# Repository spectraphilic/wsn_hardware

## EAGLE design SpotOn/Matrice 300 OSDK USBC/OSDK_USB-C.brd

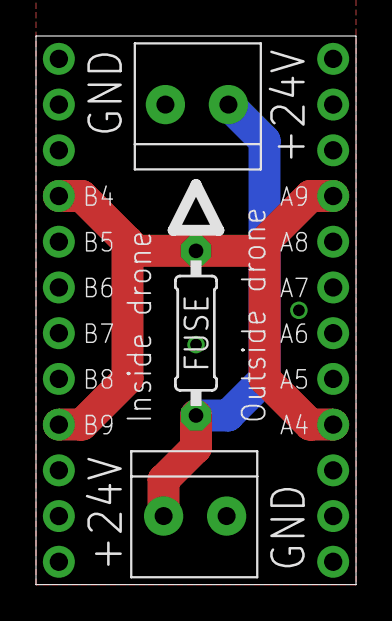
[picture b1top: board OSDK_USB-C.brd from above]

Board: 2 copper layers, 17.8 x 30.5 mm, 5 parts (0 on the bottom side), 3 nets.

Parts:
A: 1X12-CB
B: 1X12-CB
FUSE: 0207/9
J1, J2: ADAFRUIT_1X2-3.5MM

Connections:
GND: A.1, A.12, B.1, B.7, B.8, B.12, J1.2, J2.2
MAIN: A.4, A.9, B.4, B.9, FUSE.2
MIAN-F: FUSE.1, J1.1, J2.1

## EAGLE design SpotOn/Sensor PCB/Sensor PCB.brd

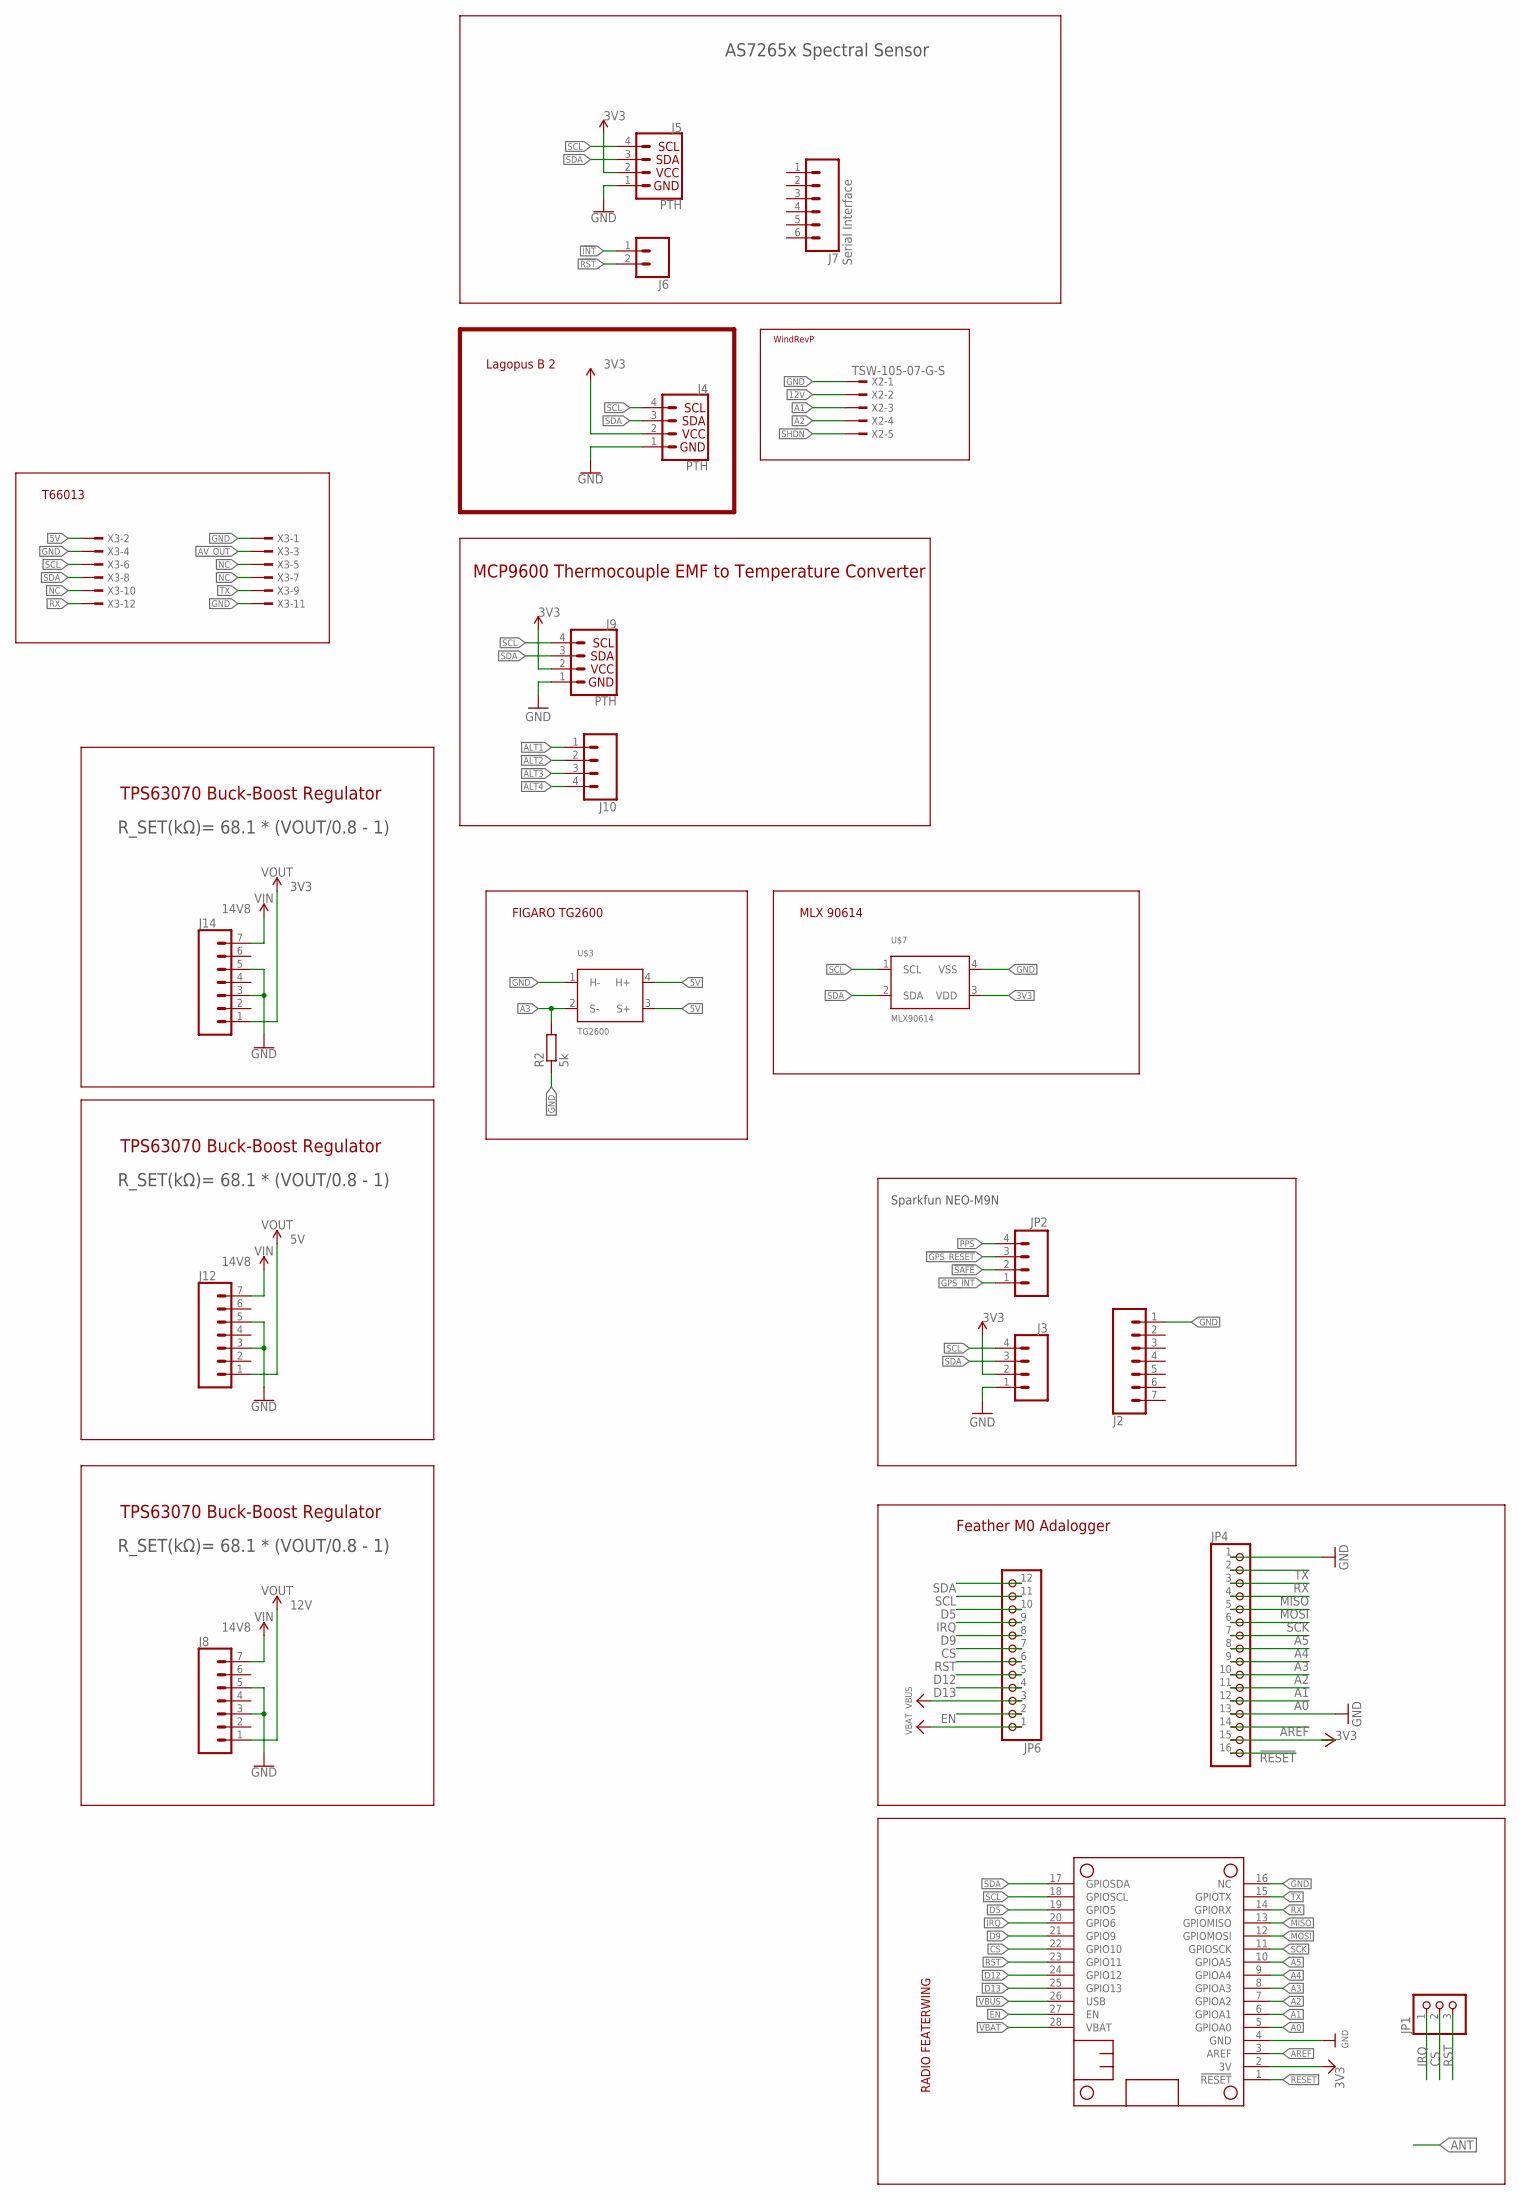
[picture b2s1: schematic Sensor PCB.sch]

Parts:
J2, J8, J12, J14: CONN_07NO_SILK; 1X07_NO_SILK
J3, J10: CONN_041X04_NO_SILK; 1X04_NO_SILK
J4, J5, J9: PTH; 1X04_NO_SILK
J6: CONN_021X02_NO_SILK; 1X02_NO_SILK
J7: Serial Interface; 1X06_NO_SILK
JP1: HEADER-1X376MIL; 1X03_ROUND_76
JP2: CONN_041X04_NO_SILK; 1X04_NO_SILK
JP4: HEADER-1X16ROUND; 1X16_ROUND
JP6: HEADER-1X12; 1X12_ROUND
MS2: FEATHERWING_NOHOLES
R2: 5k; 0207/7
U$3: TG2600; TO-5
U$7: MLX90614; TO-39
X2: TSW-105-07-G-S; TSW-105-XX-G-S
X3: TSW-106-07-G-D; TSW-106-XX-G-D

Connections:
3V3: J3.2, J4.2 (VCC), J5.2, J9.2, J14.1, JP4.15, MS2.2 (3V), U$7.3 (VDD)
5V: J12.1, U$3.3 (S+), U$3.4 (H+), X3.2
12V: J8.1, X2.2
14V8: J8.7, J12.7, J14.7
!ALT1: J10.1
!ALT2: J10.2
!ALT3: J10.3
!ALT4: J10.4
!GPS_RESET: JP2.3
!INT: J6.1
!RESET: JP4.16
!RST: J6.2
!SAFE: JP2.2
A0: JP4.12, MS2.5 (GPIOA0)
A1: JP4.11, MS2.6 (GPIOA1), X2.3
A2: JP4.10, MS2.7 (GPIOA2), X2.4
A3: JP4.9, MS2.8 (GPIOA3), R2.2, U$3.2 (S-)
A4: JP4.8, MS2.9 (GPIOA4)
A5: JP4.7, MS2.10 (GPIOA5)
AREF: JP4.14, MS2.3 (AREF)
AV_OUT: X3.3
CS: JP1.2, JP6.7, MS2.22 (GPIO10)
D5: JP6.10, MS2.19 (GPIO5)
D9: JP6.8, MS2.21 (GPIO9)
D12: JP6.5, MS2.24 (GPIO12)
D13: JP6.4, MS2.25 (GPIO13)
EN: JP6.2, MS2.27 (EN)
GND: J2.1, J3.1, J4.1 (GND), J5.1, J8.3, J8.5, J9.1, J12.3, J12.5, J14.3, J14.5, JP4.1, JP4.13, MS2.4 (GND), MS2.16 (NC), R2.1, U$3.1 (H-), U$7.4 (VSS), X2.1, X3.1, X3.4, X3.11
GPS_INT: JP2.1
IRQ: JP1.1, JP6.9, MS2.20 (GPIO6)
MISO: JP4.4, MS2.13 (GPIOMISO)
MOSI: JP4.5, MS2.12 (GPIOMOSI)
NC: X3.5, X3.7, X3.10
PPS: JP2.4
RESET: MS2.1 (!RESET)
RST: JP1.3, JP6.6, MS2.23 (GPIO11)
RX: JP4.3, MS2.14 (GPIORX), X3.12
SCK: JP4.6, MS2.11 (GPIOSCK)
SCL: J3.4, J4.4 (SCL), J5.4, J9.4, JP6.11, MS2.18 (GPIOSCL), U$7.1 (SCL), X3.6
SDA: J3.3, J4.3 (SDA), J5.3, J9.3, JP6.12, MS2.17 (GPIOSDA), U$7.2 (SDA), X3.8
SHDN: X2.5
TX: JP4.2, MS2.15 (GPIOTX), X3.9
VBAT: JP6.1, MS2.28 (VBAT)
VBUS: JP6.3, MS2.26 (USB)

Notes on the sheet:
RADIO FEATERWING
Feather M0 Adalogger
Sparkfun NEO-M9N
AS7265x Spectral Sensor
Lagopus B 2
WindRevP
MCP9600 Thermocouple EMF to Temperature Converter
T66013
TPS63070 Buck-Boost Regulator
R_SET(kΩ)= 68.1 * (VOUT/0.8 - 1)
FIGARO TG2600
MLX 90614

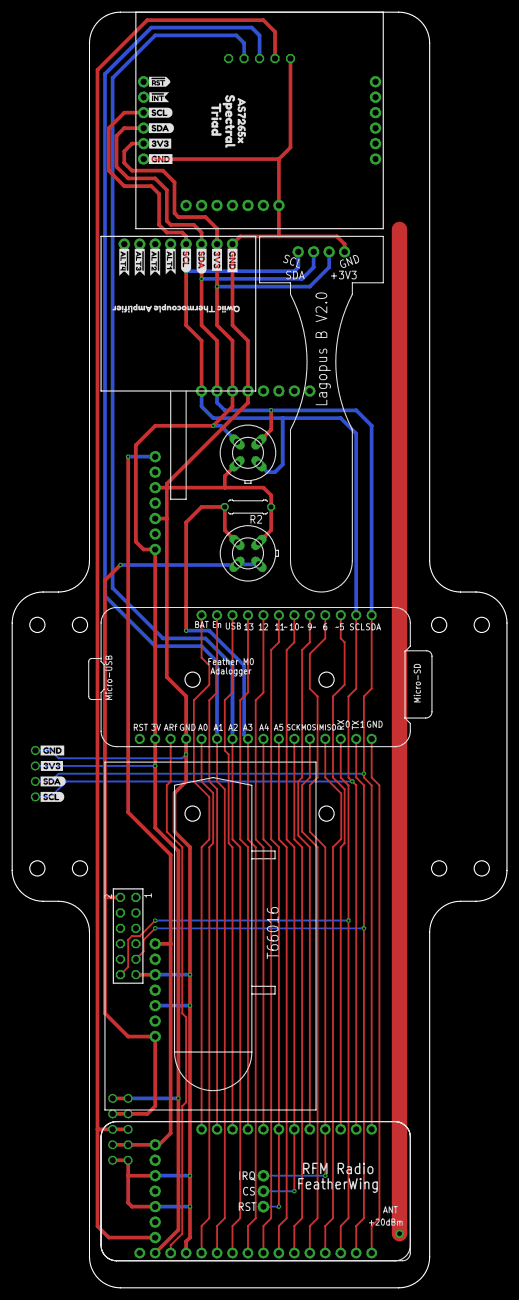
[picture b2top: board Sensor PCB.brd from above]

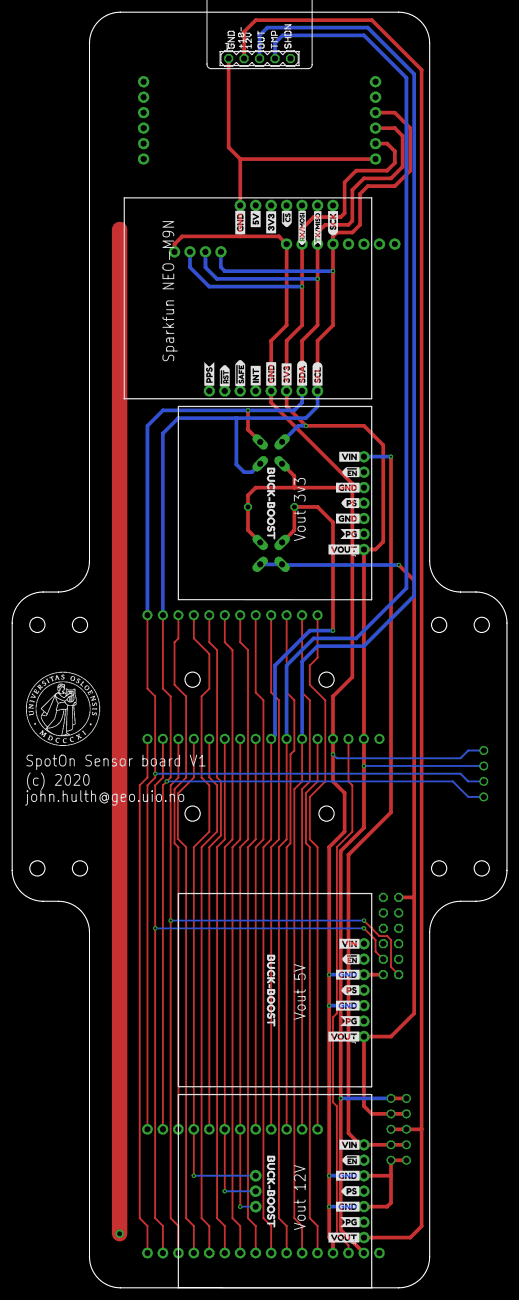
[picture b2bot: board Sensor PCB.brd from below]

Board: 2 copper layers, 81.3 x 209.6 mm, 84 parts (47 on the bottom side), 30 nets.

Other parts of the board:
U$1: UIO-LOGO-BL
U$8, U$12, U$20, U$44: GND-04
U$9, U$19, U$46: SDA-[)
U$10, U$26, U$47: SCL-[)
U$11, U$15, U$18, U$45: 3V3-04
U$13: INT8
U$14: #RST3
U$16: #SAFE1
U$17: PPS5
U$21: 5V
U$22: CS#-<]
U$23: AS7265X0
U$24: SCK-(]-04
U$25: RX#MOSI2
U$27: TX#MISO0
U$29, U$63, U$79: VIN0
U$30, U$43, U$64, U$65, U$80, U$81: GND1
U$31: GND0
U$32: 3V31
U$33: SDA2
U$34: SCL3
U$35: #ALT14
U$36: SPECTRAL1
U$37: TRIAD2
U$38: #ALT25
U$39: #ALT36
U$40: #ALT47
U$41: QWIIC_THERMOCOUPLE2
U$42: AMPLIFIER1
U$48: INT#-[<-04
U$49: RST#-[>-04
U$50, U$66, U$82: VOUT2
U$51, U$67, U$83: #EN0
U$52, U$68, U$84: PS1
U$53, U$69, U$85: PG2
U$54, U$70, U$86: BUCK#BOOST18

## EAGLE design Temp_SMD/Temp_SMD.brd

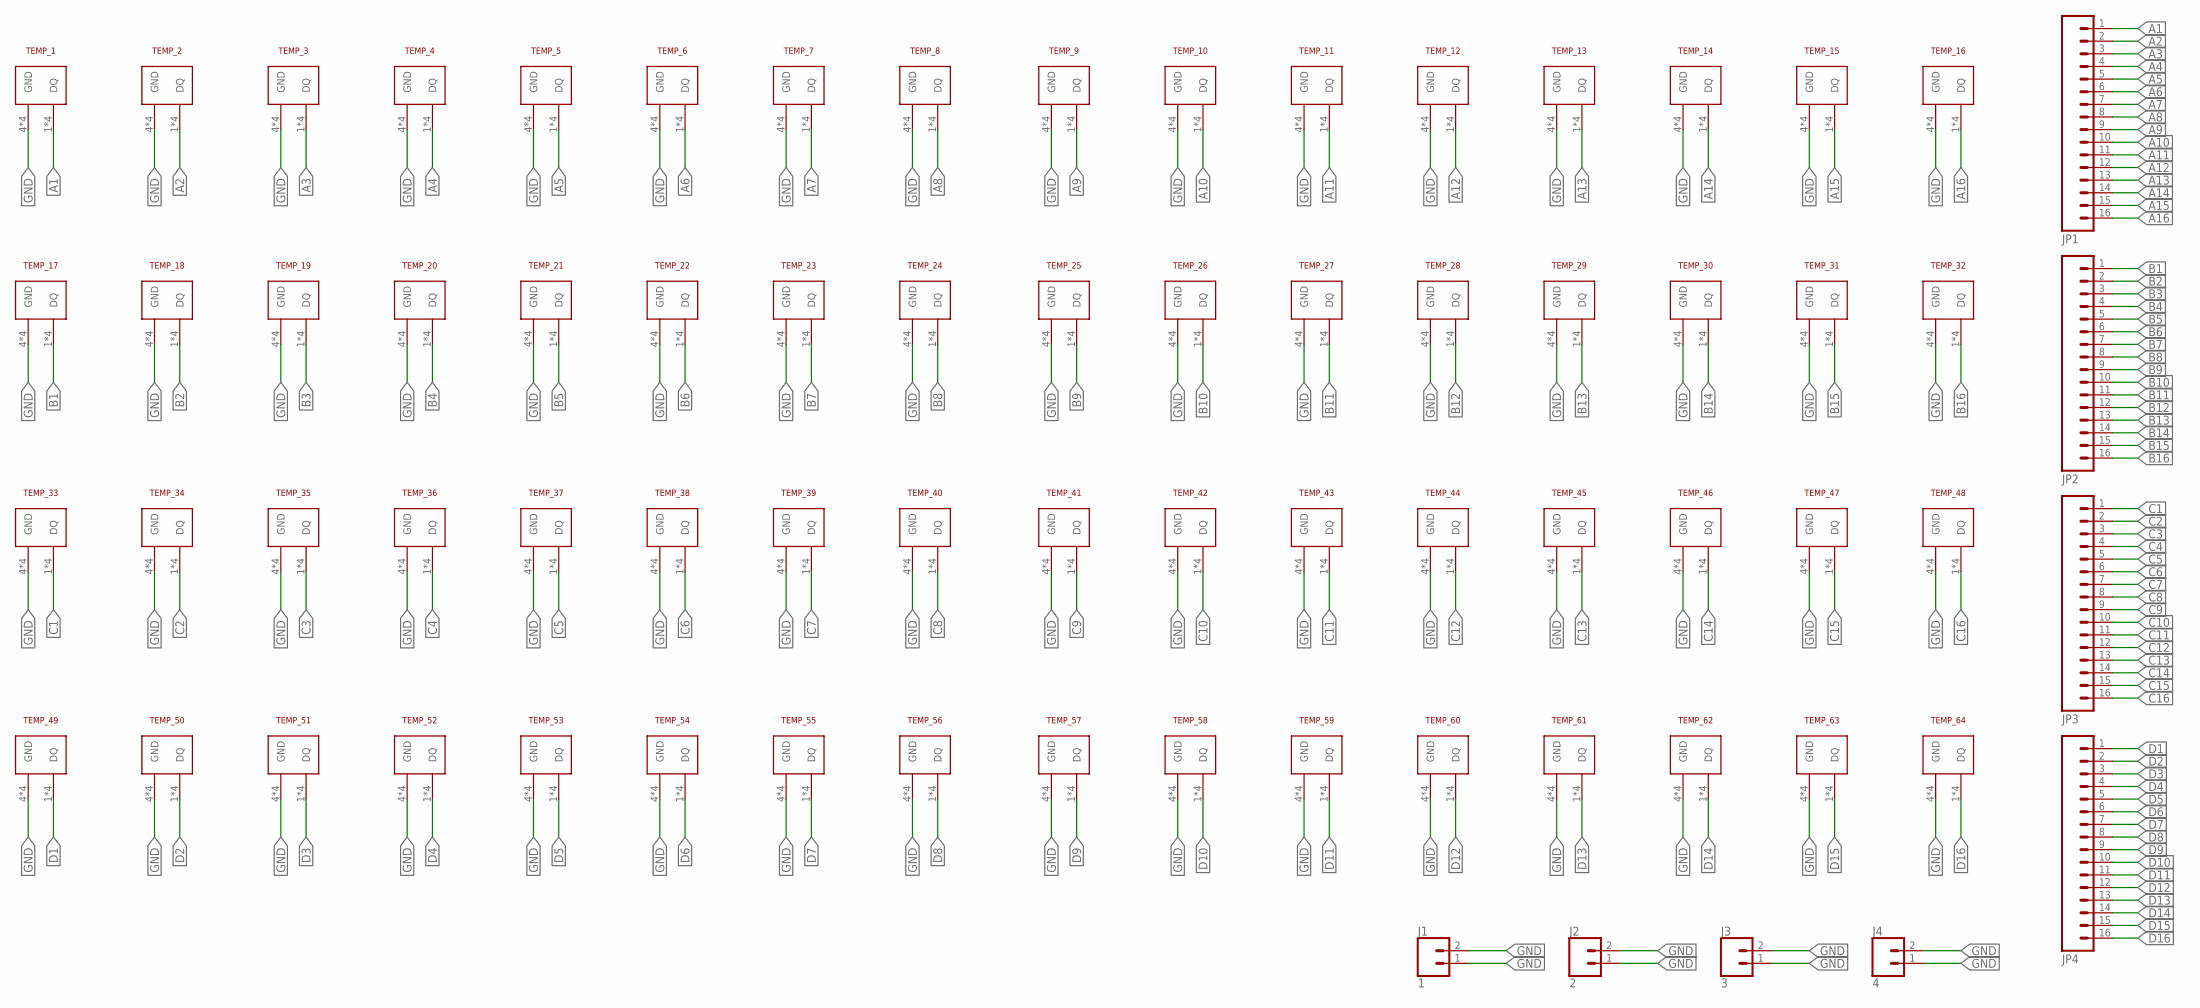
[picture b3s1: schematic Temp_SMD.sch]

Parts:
J1: 1; 1X02
J2: 2; 1X02
J3: 3; 1X02
J4: 4; 1X02
JP1, JP2, JP3, JP4: M16PTH; 1X16
TEMP_1, TEMP_2, TEMP_3, TEMP_4, TEMP_5, TEMP_6, TEMP_7, TEMP_8, TEMP_9, TEMP_10, TEMP_11, TEMP_12, TEMP_13, TEMP_14, TEMP_15, TEMP_16, TEMP_17, TEMP_18, TEMP_19, TEMP_20, TEMP_21, TEMP_22, TEMP_23, TEMP_24, TEMP_25, TEMP_26, TEMP_27, TEMP_28, TEMP_29, TEMP_30, TEMP_31, TEMP_32, TEMP_33, TEMP_34, TEMP_35, TEMP_36, TEMP_37, TEMP_38, TEMP_39, TEMP_40, TEMP_41, TEMP_42, TEMP_43, TEMP_44, TEMP_45, TEMP_46, TEMP_47, TEMP_48, TEMP_49, TEMP_50, TEMP_51, TEMP_52, TEMP_53, TEMP_54, TEMP_55, TEMP_56, TEMP_57, TEMP_58, TEMP_59, TEMP_60, TEMP_61, TEMP_62, TEMP_63, TEMP_64: SMD_TEMP

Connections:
A1: JP1.1, TEMP_1.1 (DQ), TEMP_1.DQ, TEMP_1.DQ1 (DQ), TEMP_1.DQ2 (DQ)
A2: JP1.2, TEMP_2.1 (DQ), TEMP_2.DQ, TEMP_2.DQ1 (DQ), TEMP_2.DQ2 (DQ)
A3: JP1.3, TEMP_3.1 (DQ), TEMP_3.DQ, TEMP_3.DQ1 (DQ), TEMP_3.DQ2 (DQ)
A4: JP1.4, TEMP_4.1 (DQ), TEMP_4.DQ, TEMP_4.DQ1 (DQ), TEMP_4.DQ2 (DQ)
A5: JP1.5, TEMP_5.1 (DQ), TEMP_5.DQ, TEMP_5.DQ1 (DQ), TEMP_5.DQ2 (DQ)
A6: JP1.6, TEMP_6.1 (DQ), TEMP_6.DQ, TEMP_6.DQ1 (DQ), TEMP_6.DQ2 (DQ)
A7: JP1.7, TEMP_7.1 (DQ), TEMP_7.DQ, TEMP_7.DQ1 (DQ), TEMP_7.DQ2 (DQ)
A8: JP1.8, TEMP_8.1 (DQ), TEMP_8.DQ, TEMP_8.DQ1 (DQ), TEMP_8.DQ2 (DQ)
A9: JP1.9, TEMP_9.1 (DQ), TEMP_9.DQ, TEMP_9.DQ1 (DQ), TEMP_9.DQ2 (DQ)
A10: JP1.10, TEMP_10.1 (DQ), TEMP_10.DQ, TEMP_10.DQ1 (DQ), TEMP_10.DQ2 (DQ)
A11: JP1.11, TEMP_11.1 (DQ), TEMP_11.DQ, TEMP_11.DQ1 (DQ), TEMP_11.DQ2 (DQ)
A12: JP1.12, TEMP_12.1 (DQ), TEMP_12.DQ, TEMP_12.DQ1 (DQ), TEMP_12.DQ2 (DQ)
A13: JP1.13, TEMP_13.1 (DQ), TEMP_13.DQ, TEMP_13.DQ1 (DQ), TEMP_13.DQ2 (DQ)
A14: JP1.14, TEMP_14.1 (DQ), TEMP_14.DQ, TEMP_14.DQ1 (DQ), TEMP_14.DQ2 (DQ)
A15: JP1.15, TEMP_15.1 (DQ), TEMP_15.DQ, TEMP_15.DQ1 (DQ), TEMP_15.DQ2 (DQ)
A16: JP1.16, TEMP_16.1 (DQ), TEMP_16.DQ, TEMP_16.DQ1 (DQ), TEMP_16.DQ2 (DQ)
B1: JP2.1, TEMP_17.1 (DQ), TEMP_17.DQ, TEMP_17.DQ1 (DQ), TEMP_17.DQ2 (DQ)
B2: JP2.2, TEMP_18.1 (DQ), TEMP_18.DQ, TEMP_18.DQ1 (DQ), TEMP_18.DQ2 (DQ)
B3: JP2.3, TEMP_19.1 (DQ), TEMP_19.DQ, TEMP_19.DQ1 (DQ), TEMP_19.DQ2 (DQ)
B4: JP2.4, TEMP_20.1 (DQ), TEMP_20.DQ, TEMP_20.DQ1 (DQ), TEMP_20.DQ2 (DQ)
B5: JP2.5, TEMP_21.1 (DQ), TEMP_21.DQ, TEMP_21.DQ1 (DQ), TEMP_21.DQ2 (DQ)
B6: JP2.6, TEMP_22.1 (DQ), TEMP_22.DQ, TEMP_22.DQ1 (DQ), TEMP_22.DQ2 (DQ)
B7: JP2.7, TEMP_23.1 (DQ), TEMP_23.DQ, TEMP_23.DQ1 (DQ), TEMP_23.DQ2 (DQ)
B8: JP2.8, TEMP_24.1 (DQ), TEMP_24.DQ, TEMP_24.DQ1 (DQ), TEMP_24.DQ2 (DQ)
B9: JP2.9, TEMP_25.1 (DQ), TEMP_25.DQ, TEMP_25.DQ1 (DQ), TEMP_25.DQ2 (DQ)
B10: JP2.10, TEMP_26.1 (DQ), TEMP_26.DQ, TEMP_26.DQ1 (DQ), TEMP_26.DQ2 (DQ)
B11: JP2.11, TEMP_27.1 (DQ), TEMP_27.DQ, TEMP_27.DQ1 (DQ), TEMP_27.DQ2 (DQ)
B12: JP2.12, TEMP_28.1 (DQ), TEMP_28.DQ, TEMP_28.DQ1 (DQ), TEMP_28.DQ2 (DQ)
B13: JP2.13, TEMP_29.1 (DQ), TEMP_29.DQ, TEMP_29.DQ1 (DQ), TEMP_29.DQ2 (DQ)
B14: JP2.14, TEMP_30.1 (DQ), TEMP_30.DQ, TEMP_30.DQ1 (DQ), TEMP_30.DQ2 (DQ)
B15: JP2.15, TEMP_31.1 (DQ), TEMP_31.DQ, TEMP_31.DQ1 (DQ), TEMP_31.DQ2 (DQ)
B16: JP2.16, TEMP_32.1 (DQ), TEMP_32.DQ, TEMP_32.DQ1 (DQ), TEMP_32.DQ2 (DQ)
C1: JP3.1, TEMP_33.1 (DQ), TEMP_33.DQ, TEMP_33.DQ1 (DQ), TEMP_33.DQ2 (DQ)
C2: JP3.2, TEMP_34.1 (DQ), TEMP_34.DQ, TEMP_34.DQ1 (DQ), TEMP_34.DQ2 (DQ)
C3: JP3.3, TEMP_35.1 (DQ), TEMP_35.DQ, TEMP_35.DQ1 (DQ), TEMP_35.DQ2 (DQ)
C4: JP3.4, TEMP_36.1 (DQ), TEMP_36.DQ, TEMP_36.DQ1 (DQ), TEMP_36.DQ2 (DQ)
C5: JP3.5, TEMP_37.1 (DQ), TEMP_37.DQ, TEMP_37.DQ1 (DQ), TEMP_37.DQ2 (DQ)
C6: JP3.6, TEMP_38.1 (DQ), TEMP_38.DQ, TEMP_38.DQ1 (DQ), TEMP_38.DQ2 (DQ)
C7: JP3.7, TEMP_39.1 (DQ), TEMP_39.DQ, TEMP_39.DQ1 (DQ), TEMP_39.DQ2 (DQ)
C8: JP3.8, TEMP_40.1 (DQ), TEMP_40.DQ, TEMP_40.DQ1 (DQ), TEMP_40.DQ2 (DQ)
C9: JP3.9, TEMP_41.1 (DQ), TEMP_41.DQ, TEMP_41.DQ1 (DQ), TEMP_41.DQ2 (DQ)
C10: JP3.10, TEMP_42.1 (DQ), TEMP_42.DQ, TEMP_42.DQ1 (DQ), TEMP_42.DQ2 (DQ)
C11: JP3.11, TEMP_43.1 (DQ), TEMP_43.DQ, TEMP_43.DQ1 (DQ), TEMP_43.DQ2 (DQ)
C12: JP3.12, TEMP_44.1 (DQ), TEMP_44.DQ, TEMP_44.DQ1 (DQ), TEMP_44.DQ2 (DQ)
C13: JP3.13, TEMP_45.1 (DQ), TEMP_45.DQ, TEMP_45.DQ1 (DQ), TEMP_45.DQ2 (DQ)
C14: JP3.14, TEMP_46.1 (DQ), TEMP_46.DQ, TEMP_46.DQ1 (DQ), TEMP_46.DQ2 (DQ)
C15: JP3.15, TEMP_47.1 (DQ), TEMP_47.DQ, TEMP_47.DQ1 (DQ), TEMP_47.DQ2 (DQ)
C16: JP3.16, TEMP_48.1 (DQ), TEMP_48.DQ, TEMP_48.DQ1 (DQ), TEMP_48.DQ2 (DQ)
D1: JP4.1, TEMP_49.1 (DQ), TEMP_49.DQ, TEMP_49.DQ1 (DQ), TEMP_49.DQ2 (DQ)
D2: JP4.2, TEMP_50.1 (DQ), TEMP_50.DQ, TEMP_50.DQ1 (DQ), TEMP_50.DQ2 (DQ)
D3: JP4.3, TEMP_51.1 (DQ), TEMP_51.DQ, TEMP_51.DQ1 (DQ), TEMP_51.DQ2 (DQ)
D4: JP4.4, TEMP_52.1 (DQ), TEMP_52.DQ, TEMP_52.DQ1 (DQ), TEMP_52.DQ2 (DQ)
D5: JP4.5, TEMP_53.1 (DQ), TEMP_53.DQ, TEMP_53.DQ1 (DQ), TEMP_53.DQ2 (DQ)
D6: JP4.6, TEMP_54.1 (DQ), TEMP_54.DQ, TEMP_54.DQ1 (DQ), TEMP_54.DQ2 (DQ)
D7: JP4.7, TEMP_55.1 (DQ), TEMP_55.DQ, TEMP_55.DQ1 (DQ), TEMP_55.DQ2 (DQ)
D8: JP4.8, TEMP_56.1 (DQ), TEMP_56.DQ, TEMP_56.DQ1 (DQ), TEMP_56.DQ2 (DQ)
D9: JP4.9, TEMP_57.1 (DQ), TEMP_57.DQ, TEMP_57.DQ1 (DQ), TEMP_57.DQ2 (DQ)
D10: JP4.10, TEMP_58.1 (DQ), TEMP_58.DQ, TEMP_58.DQ1 (DQ), TEMP_58.DQ2 (DQ)
D11: JP4.11, TEMP_59.1 (DQ), TEMP_59.DQ, TEMP_59.DQ1 (DQ), TEMP_59.DQ2 (DQ)
D12: JP4.12, TEMP_60.1 (DQ), TEMP_60.DQ, TEMP_60.DQ1 (DQ), TEMP_60.DQ2 (DQ)
D13: JP4.13, TEMP_61.1 (DQ), TEMP_61.DQ, TEMP_61.DQ1 (DQ), TEMP_61.DQ2 (DQ)
D14: JP4.14, TEMP_62.1 (DQ), TEMP_62.DQ, TEMP_62.DQ1 (DQ), TEMP_62.DQ2 (DQ)
D15: JP4.15, TEMP_63.1 (DQ), TEMP_63.DQ, TEMP_63.DQ1 (DQ), TEMP_63.DQ2 (DQ)
D16: JP4.16, TEMP_64.1 (DQ), TEMP_64.DQ, TEMP_64.DQ1 (DQ), TEMP_64.DQ2 (DQ)
GND: J1.1, J1.2, J2.1, J2.2, J3.1, J3.2, J4.1, J4.2, TEMP_1.4 (GND), TEMP_1.8 (GND), TEMP_1.GND1 (GND), TEMP_1.GND2 (GND), TEMP_2.4 (GND), TEMP_2.8 (GND), TEMP_2.GND1 (GND), TEMP_2.GND2 (GND), TEMP_3.4 (GND), TEMP_3.8 (GND), TEMP_3.GND1 (GND), TEMP_3.GND2 (GND), TEMP_4.4 (GND), TEMP_4.8 (GND), TEMP_4.GND1 (GND), TEMP_4.GND2 (GND), TEMP_5.4 (GND), TEMP_5.8 (GND), TEMP_5.GND1 (GND), TEMP_5.GND2 (GND), TEMP_6.4 (GND), TEMP_6.8 (GND), TEMP_6.GND1 (GND), TEMP_6.GND2 (GND), TEMP_7.4 (GND), TEMP_7.8 (GND), TEMP_7.GND1 (GND), TEMP_7.GND2 (GND), TEMP_8.4 (GND), TEMP_8.8 (GND), TEMP_8.GND1 (GND), TEMP_8.GND2 (GND), TEMP_9.4 (GND), TEMP_9.8 (GND), TEMP_9.GND1 (GND), TEMP_9.GND2 (GND), TEMP_10.4 (GND), TEMP_10.8 (GND), TEMP_10.GND1 (GND), TEMP_10.GND2 (GND), TEMP_11.4 (GND), TEMP_11.8 (GND), TEMP_11.GND1 (GND), TEMP_11.GND2 (GND), TEMP_12.4 (GND), TEMP_12.8 (GND), TEMP_12.GND1 (GND), TEMP_12.GND2 (GND), TEMP_13.4 (GND), TEMP_13.8 (GND), TEMP_13.GND1 (GND), TEMP_13.GND2 (GND), TEMP_14.4 (GND), TEMP_14.8 (GND), TEMP_14.GND1 (GND), TEMP_14.GND2 (GND), TEMP_15.4 (GND), TEMP_15.8 (GND), TEMP_15.GND1 (GND), TEMP_15.GND2 (GND), TEMP_16.4 (GND), TEMP_16.8 (GND), TEMP_16.GND1 (GND), TEMP_16.GND2 (GND), TEMP_17.4 (GND), TEMP_17.8 (GND), TEMP_17.GND1 (GND), TEMP_17.GND2 (GND), TEMP_18.4 (GND), TEMP_18.8 (GND), TEMP_18.GND1 (GND), TEMP_18.GND2 (GND), TEMP_19.4 (GND), TEMP_19.8 (GND), TEMP_19.GND1 (GND), TEMP_19.GND2 (GND), TEMP_20.4 (GND), TEMP_20.8 (GND), TEMP_20.GND1 (GND), TEMP_20.GND2 (GND), TEMP_21.4 (GND), TEMP_21.8 (GND), TEMP_21.GND1 (GND), TEMP_21.GND2 (GND), TEMP_22.4 (GND), TEMP_22.8 (GND), TEMP_22.GND1 (GND), TEMP_22.GND2 (GND), TEMP_23.4 (GND), TEMP_23.8 (GND), TEMP_23.GND1 (GND), TEMP_23.GND2 (GND), TEMP_24.4 (GND), TEMP_24.8 (GND), TEMP_24.GND1 (GND), TEMP_24.GND2 (GND), TEMP_25.4 (GND), TEMP_25.8 (GND), TEMP_25.GND1 (GND), TEMP_25.GND2 (GND), TEMP_26.4 (GND), TEMP_26.8 (GND), TEMP_26.GND1 (GND), TEMP_26.GND2 (GND), TEMP_27.4 (GND)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

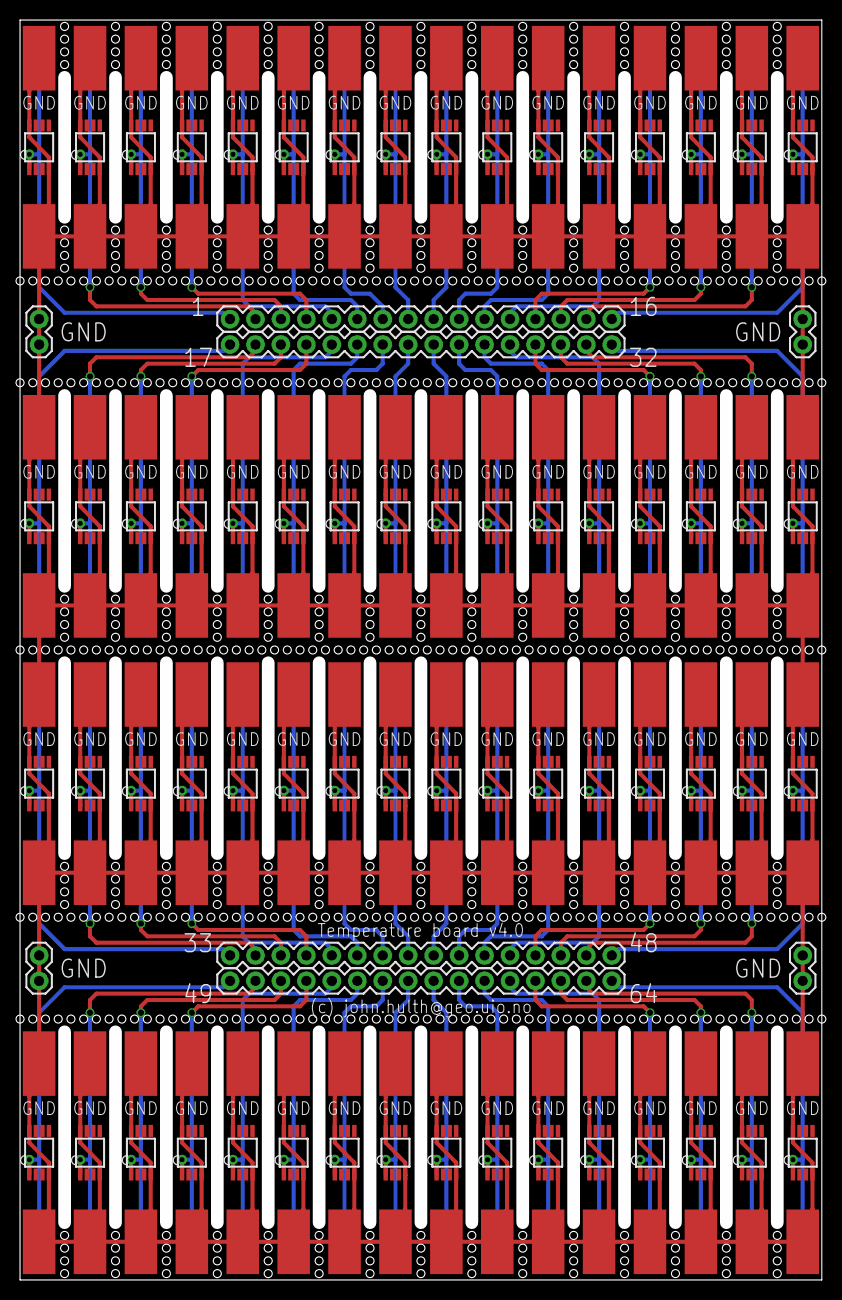
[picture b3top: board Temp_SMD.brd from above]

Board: 2 copper layers, 80.0 x 125.7 mm, 72 parts (0 on the bottom side), 65 nets.

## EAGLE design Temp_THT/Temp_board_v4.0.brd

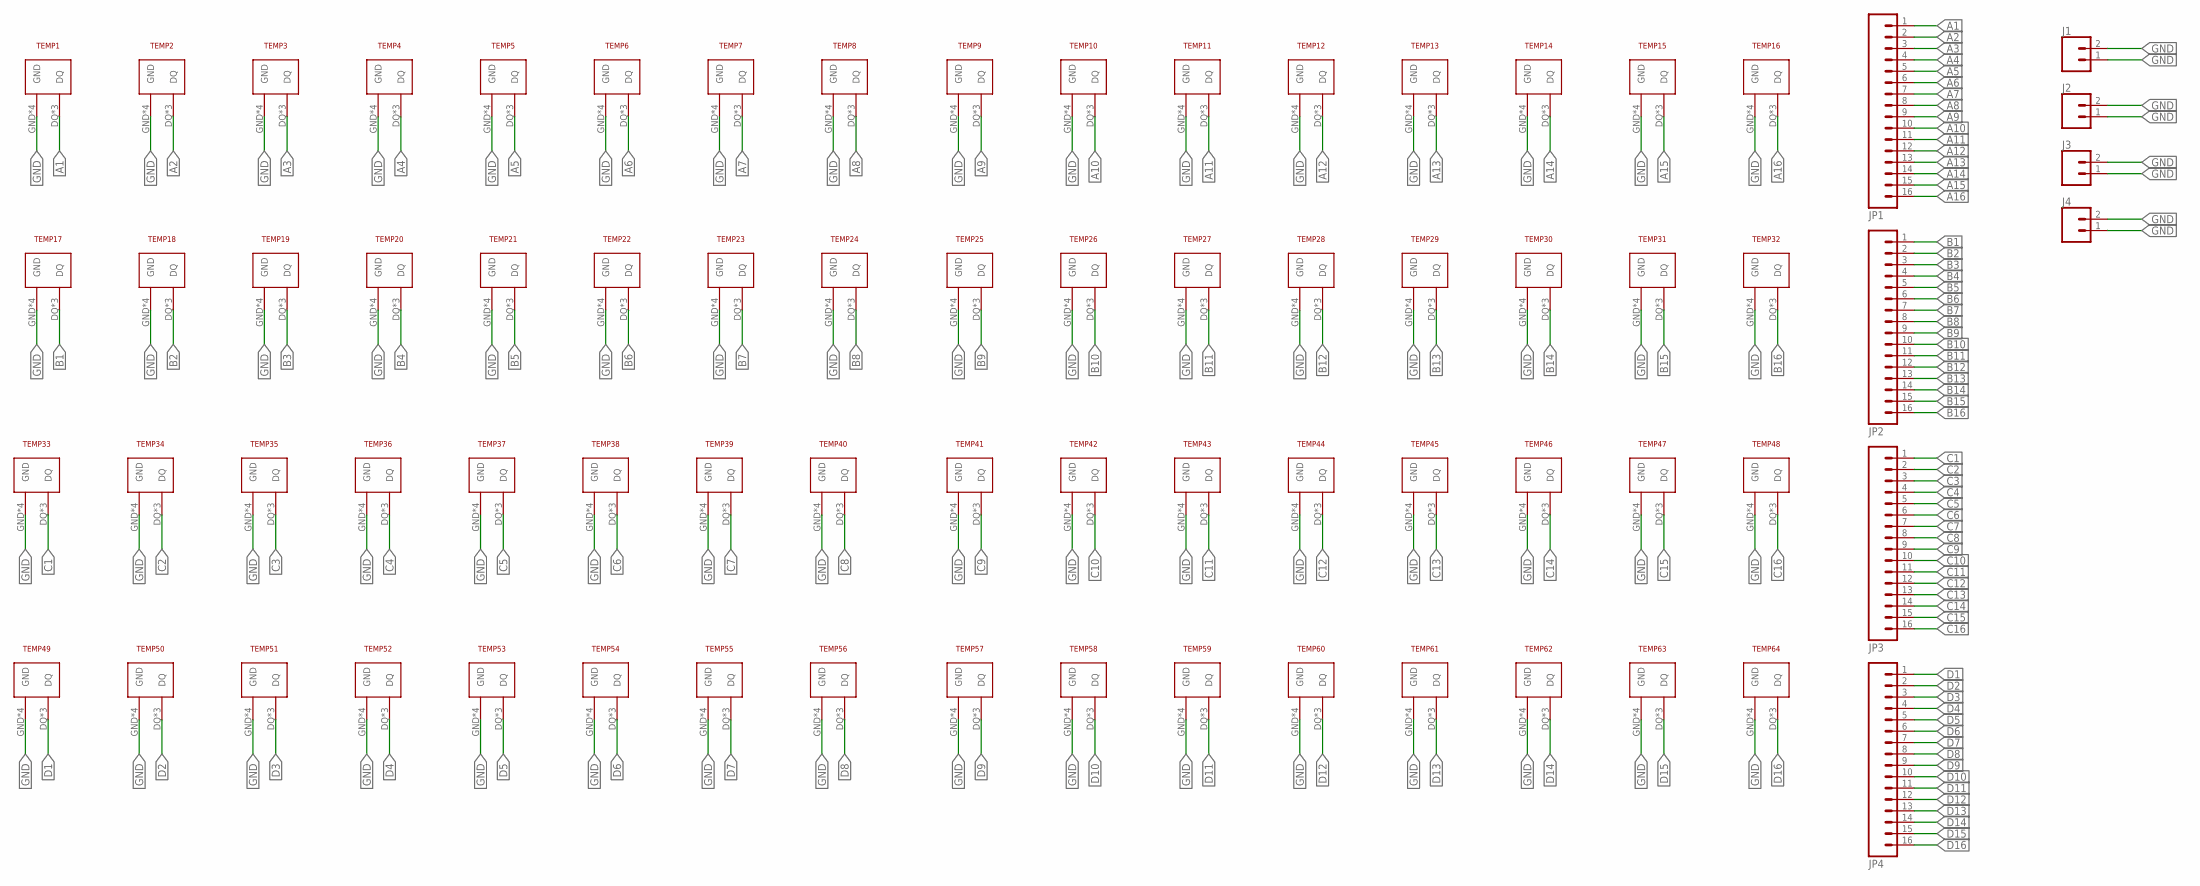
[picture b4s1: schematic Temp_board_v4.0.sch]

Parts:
J1, J2, J3, J4: CONN_02; 1X02
JP1, JP2, JP3, JP4: M16PTH; 1X16
TEMP1, TEMP2, TEMP3, TEMP4, TEMP5, TEMP6, TEMP7, TEMP8, TEMP9, TEMP10, TEMP11, TEMP12, TEMP13, TEMP14, TEMP15, TEMP16, TEMP17, TEMP18, TEMP19, TEMP20, TEMP21, TEMP22, TEMP23, TEMP24, TEMP25, TEMP26, TEMP27, TEMP28, TEMP29, TEMP30, TEMP31, TEMP32, TEMP33, TEMP34, TEMP35, TEMP36, TEMP37, TEMP38, TEMP39, TEMP40, TEMP41, TEMP42, TEMP43, TEMP44, TEMP45, TEMP46, TEMP47, TEMP48, TEMP49, TEMP50, TEMP51, TEMP52, TEMP53, TEMP54, TEMP55, TEMP56, TEMP57, TEMP58, TEMP59, TEMP60, TEMP61, TEMP62, TEMP63, TEMP64: TEMP_TEST_ALL; TEMP_TEST_PACKAGE

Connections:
A1: JP1.1, TEMP1.DQ, TEMP1.DQ1 (DQ), TEMP1.DQ2 (DQ)
A2: JP1.2, TEMP2.DQ, TEMP2.DQ1 (DQ), TEMP2.DQ2 (DQ)
A3: JP1.3, TEMP3.DQ, TEMP3.DQ1 (DQ), TEMP3.DQ2 (DQ)
A4: JP1.4, TEMP4.DQ, TEMP4.DQ1 (DQ), TEMP4.DQ2 (DQ)
A5: JP1.5, TEMP5.DQ, TEMP5.DQ1 (DQ), TEMP5.DQ2 (DQ)
A6: JP1.6, TEMP6.DQ, TEMP6.DQ1 (DQ), TEMP6.DQ2 (DQ)
A7: JP1.7, TEMP7.DQ, TEMP7.DQ1 (DQ), TEMP7.DQ2 (DQ)
A8: JP1.8, TEMP8.DQ, TEMP8.DQ1 (DQ), TEMP8.DQ2 (DQ)
A9: JP1.9, TEMP9.DQ, TEMP9.DQ1 (DQ), TEMP9.DQ2 (DQ)
A10: JP1.10, TEMP10.DQ, TEMP10.DQ1 (DQ), TEMP10.DQ2 (DQ)
A11: JP1.11, TEMP11.DQ, TEMP11.DQ1 (DQ), TEMP11.DQ2 (DQ)
A12: JP1.12, TEMP12.DQ, TEMP12.DQ1 (DQ), TEMP12.DQ2 (DQ)
A13: JP1.13, TEMP13.DQ, TEMP13.DQ1 (DQ), TEMP13.DQ2 (DQ)
A14: JP1.14, TEMP14.DQ, TEMP14.DQ1 (DQ), TEMP14.DQ2 (DQ)
A15: JP1.15, TEMP15.DQ, TEMP15.DQ1 (DQ), TEMP15.DQ2 (DQ)
A16: JP1.16, TEMP16.DQ, TEMP16.DQ1 (DQ), TEMP16.DQ2 (DQ)
B1: JP2.1, TEMP17.DQ, TEMP17.DQ1 (DQ), TEMP17.DQ2 (DQ)
B2: JP2.2, TEMP18.DQ, TEMP18.DQ1 (DQ), TEMP18.DQ2 (DQ)
B3: JP2.3, TEMP19.DQ, TEMP19.DQ1 (DQ), TEMP19.DQ2 (DQ)
B4: JP2.4, TEMP20.DQ, TEMP20.DQ1 (DQ), TEMP20.DQ2 (DQ)
B5: JP2.5, TEMP21.DQ, TEMP21.DQ1 (DQ), TEMP21.DQ2 (DQ)
B6: JP2.6, TEMP22.DQ, TEMP22.DQ1 (DQ), TEMP22.DQ2 (DQ)
B7: JP2.7, TEMP23.DQ, TEMP23.DQ1 (DQ), TEMP23.DQ2 (DQ)
B8: JP2.8, TEMP24.DQ, TEMP24.DQ1 (DQ), TEMP24.DQ2 (DQ)
B9: JP2.9, TEMP25.DQ, TEMP25.DQ1 (DQ), TEMP25.DQ2 (DQ)
B10: JP2.10, TEMP26.DQ, TEMP26.DQ1 (DQ), TEMP26.DQ2 (DQ)
B11: JP2.11, TEMP27.DQ, TEMP27.DQ1 (DQ), TEMP27.DQ2 (DQ)
B12: JP2.12, TEMP28.DQ, TEMP28.DQ1 (DQ), TEMP28.DQ2 (DQ)
B13: JP2.13, TEMP29.DQ, TEMP29.DQ1 (DQ), TEMP29.DQ2 (DQ)
B14: JP2.14, TEMP30.DQ, TEMP30.DQ1 (DQ), TEMP30.DQ2 (DQ)
B15: JP2.15, TEMP31.DQ, TEMP31.DQ1 (DQ), TEMP31.DQ2 (DQ)
B16: JP2.16, TEMP32.DQ, TEMP32.DQ1 (DQ), TEMP32.DQ2 (DQ)
C1: JP3.1, TEMP33.DQ, TEMP33.DQ1 (DQ), TEMP33.DQ2 (DQ)
C2: JP3.2, TEMP34.DQ, TEMP34.DQ1 (DQ), TEMP34.DQ2 (DQ)
C3: JP3.3, TEMP35.DQ, TEMP35.DQ1 (DQ), TEMP35.DQ2 (DQ)
C4: JP3.4, TEMP36.DQ, TEMP36.DQ1 (DQ), TEMP36.DQ2 (DQ)
C5: JP3.5, TEMP37.DQ, TEMP37.DQ1 (DQ), TEMP37.DQ2 (DQ)
C6: JP3.6, TEMP38.DQ, TEMP38.DQ1 (DQ), TEMP38.DQ2 (DQ)
C7: JP3.7, TEMP39.DQ, TEMP39.DQ1 (DQ), TEMP39.DQ2 (DQ)
C8: JP3.8, TEMP40.DQ, TEMP40.DQ1 (DQ), TEMP40.DQ2 (DQ)
C9: JP3.9, TEMP41.DQ, TEMP41.DQ1 (DQ), TEMP41.DQ2 (DQ)
C10: JP3.10, TEMP42.DQ, TEMP42.DQ1 (DQ), TEMP42.DQ2 (DQ)
C11: JP3.11, TEMP43.DQ, TEMP43.DQ1 (DQ), TEMP43.DQ2 (DQ)
C12: JP3.12, TEMP44.DQ, TEMP44.DQ1 (DQ), TEMP44.DQ2 (DQ)
C13: JP3.13, TEMP45.DQ, TEMP45.DQ1 (DQ), TEMP45.DQ2 (DQ)
C14: JP3.14, TEMP46.DQ, TEMP46.DQ1 (DQ), TEMP46.DQ2 (DQ)
C15: JP3.15, TEMP47.DQ, TEMP47.DQ1 (DQ), TEMP47.DQ2 (DQ)
C16: JP3.16, TEMP48.DQ, TEMP48.DQ1 (DQ), TEMP48.DQ2 (DQ)
D1: JP4.1, TEMP49.DQ, TEMP49.DQ1 (DQ), TEMP49.DQ2 (DQ)
D2: JP4.2, TEMP50.DQ, TEMP50.DQ1 (DQ), TEMP50.DQ2 (DQ)
D3: JP4.3, TEMP51.DQ, TEMP51.DQ1 (DQ), TEMP51.DQ2 (DQ)
D4: JP4.4, TEMP52.DQ, TEMP52.DQ1 (DQ), TEMP52.DQ2 (DQ)
D5: JP4.5, TEMP53.DQ, TEMP53.DQ1 (DQ), TEMP53.DQ2 (DQ)
D6: JP4.6, TEMP54.DQ, TEMP54.DQ1 (DQ), TEMP54.DQ2 (DQ)
D7: JP4.7, TEMP55.DQ, TEMP55.DQ1 (DQ), TEMP55.DQ2 (DQ)
D8: JP4.8, TEMP56.DQ, TEMP56.DQ1 (DQ), TEMP56.DQ2 (DQ)
D9: JP4.9, TEMP57.DQ, TEMP57.DQ1 (DQ), TEMP57.DQ2 (DQ)
D10: JP4.10, TEMP58.DQ, TEMP58.DQ1 (DQ), TEMP58.DQ2 (DQ)
D11: JP4.11, TEMP59.DQ, TEMP59.DQ1 (DQ), TEMP59.DQ2 (DQ)
D12: JP4.12, TEMP60.DQ, TEMP60.DQ1 (DQ), TEMP60.DQ2 (DQ)
D13: JP4.13, TEMP61.DQ, TEMP61.DQ1 (DQ), TEMP61.DQ2 (DQ)
D14: JP4.14, TEMP62.DQ, TEMP62.DQ1 (DQ), TEMP62.DQ2 (DQ)
D15: JP4.15, TEMP63.DQ, TEMP63.DQ1 (DQ), TEMP63.DQ2 (DQ)
D16: JP4.16, TEMP64.DQ, TEMP64.DQ1 (DQ), TEMP64.DQ2 (DQ)
GND: J1.1, J1.2, J2.1, J2.2, J3.1, J3.2, J4.1, J4.2, TEMP1.GND, TEMP1.GND1 (GND), TEMP1.GND2 (GND), TEMP1.VDD (GND), TEMP2.GND, TEMP2.GND1 (GND), TEMP2.GND2 (GND), TEMP2.VDD (GND), TEMP3.GND, TEMP3.GND1 (GND), TEMP3.GND2 (GND), TEMP3.VDD (GND), TEMP4.GND, TEMP4.GND1 (GND), TEMP4.GND2 (GND), TEMP4.VDD (GND), TEMP5.GND, TEMP5.GND1 (GND), TEMP5.GND2 (GND), TEMP5.VDD (GND), TEMP6.GND, TEMP6.GND1 (GND), TEMP6.GND2 (GND), TEMP6.VDD (GND), TEMP7.GND, TEMP7.GND1 (GND), TEMP7.GND2 (GND), TEMP7.VDD (GND), TEMP8.GND, TEMP8.GND1 (GND), TEMP8.GND2 (GND), TEMP8.VDD (GND), TEMP9.GND, TEMP9.GND1 (GND), TEMP9.GND2 (GND), TEMP9.VDD (GND), TEMP10.GND, TEMP10.GND1 (GND), TEMP10.GND2 (GND), TEMP10.VDD (GND), TEMP11.GND, TEMP11.GND1 (GND), TEMP11.GND2 (GND), TEMP11.VDD (GND), TEMP12.GND, TEMP12.GND1 (GND), TEMP12.GND2 (GND), TEMP12.VDD (GND), TEMP13.GND, TEMP13.GND1 (GND), TEMP13.GND2 (GND), TEMP13.VDD (GND), TEMP14.GND, TEMP14.GND1 (GND), TEMP14.GND2 (GND), TEMP14.VDD (GND), TEMP15.GND, TEMP15.GND1 (GND), TEMP15.GND2 (GND), TEMP15.VDD (GND), TEMP16.GND, TEMP16.GND1 (GND), TEMP16.GND2 (GND), TEMP16.VDD (GND), TEMP17.GND, TEMP17.GND1 (GND), TEMP17.GND2 (GND), TEMP17.VDD (GND), TEMP18.GND, TEMP18.GND1 (GND), TEMP18.GND2 (GND), TEMP18.VDD (GND), TEMP19.GND, TEMP19.GND1 (GND), TEMP19.GND2 (GND), TEMP19.VDD (GND), TEMP20.GND, TEMP20.GND1 (GND), TEMP20.GND2 (GND), TEMP20.VDD (GND), TEMP21.GND, TEMP21.GND1 (GND), TEMP21.GND2 (GND), TEMP21.VDD (GND), TEMP22.GND, TEMP22.GND1 (GND), TEMP22.GND2 (GND), TEMP22.VDD (GND), TEMP23.GND, TEMP23.GND1 (GND), TEMP23.GND2 (GND), TEMP23.VDD (GND), TEMP24.GND, TEMP24.GND1 (GND), TEMP24.GND2 (GND), TEMP24.VDD (GND), TEMP25.GND, TEMP25.GND1 (GND), TEMP25.GND2 (GND), TEMP25.VDD (GND), TEMP26.GND, TEMP26.GND1 (GND), TEMP26.GND2 (GND), TEMP26.VDD (GND), TEMP27.GND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

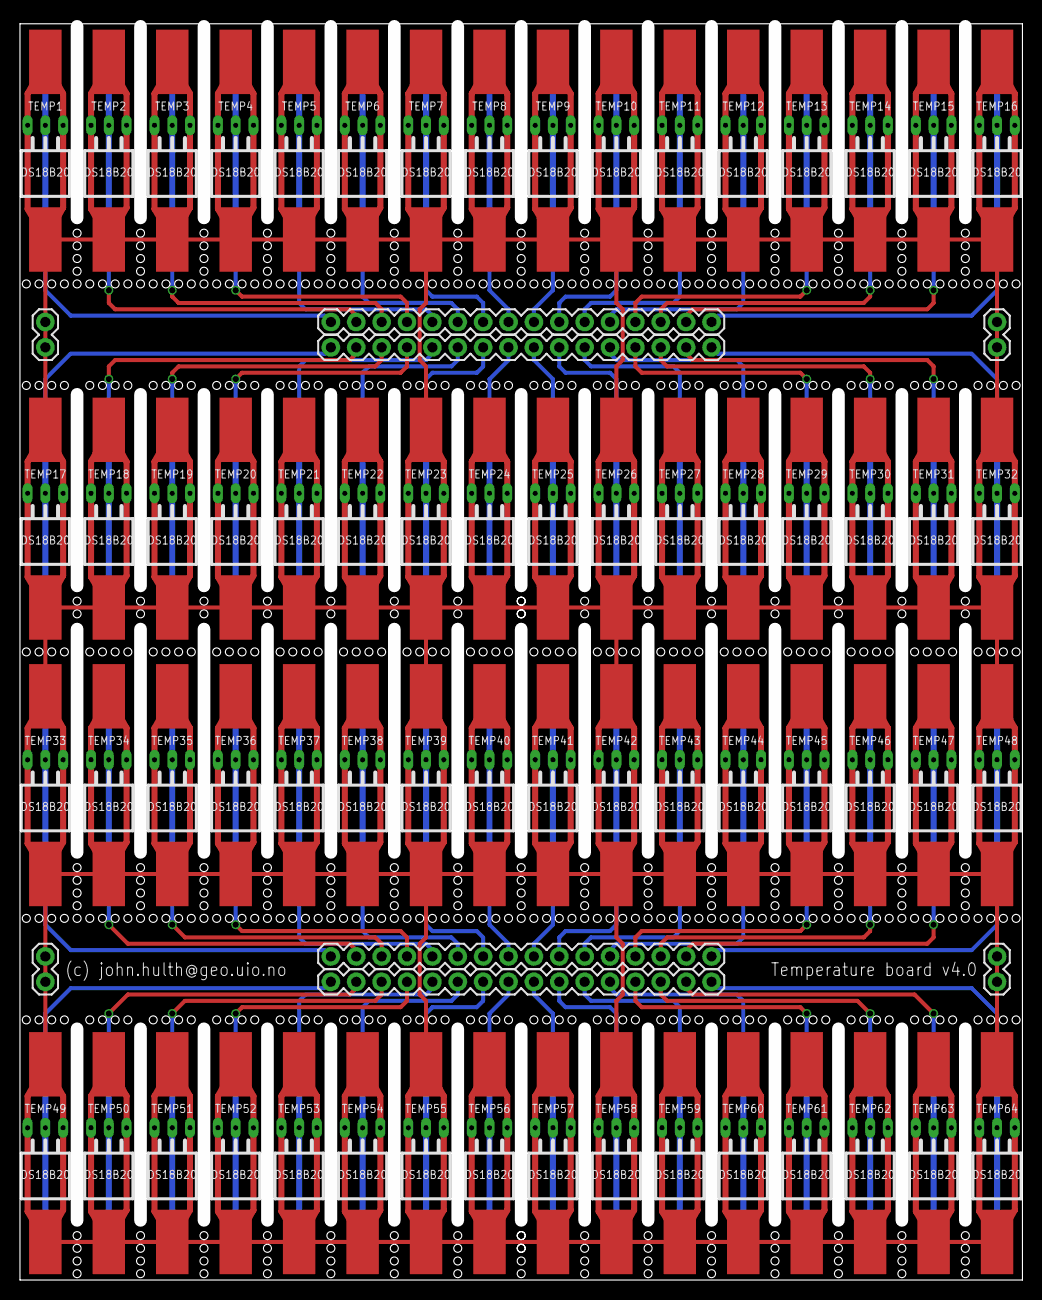
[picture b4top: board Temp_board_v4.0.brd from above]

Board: 2 copper layers, 100.3 x 125.7 mm, 72 parts (0 on the bottom side), 65 nets.

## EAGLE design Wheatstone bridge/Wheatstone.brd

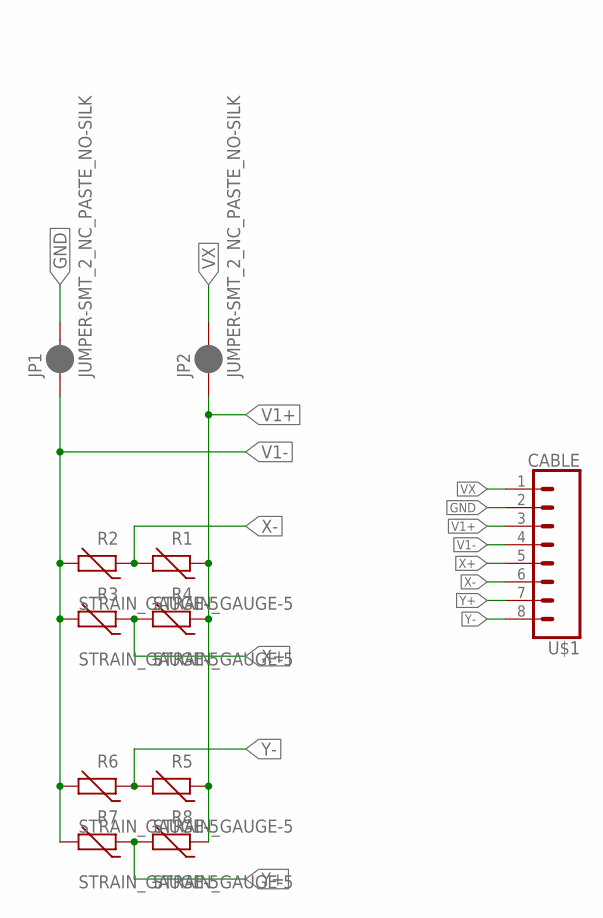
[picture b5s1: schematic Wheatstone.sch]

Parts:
JP1, JP2: JUMPER-SMT_2_NC_PASTE_NO-SILK; SMT-JUMPER_2_NC_PASTE_NO-SILK
R1, R2, R3, R4, R5, R6, R7, R8: STRAIN_GAUGE-5; STRAIN_GAUGE
U$1: CABLE

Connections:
GND: JP1.2, U$1.2
V1+: JP2.1, R1.1, R4.1, R5.1, R8.1, U$1.3
V1-: JP1.1, R2.2, R3.2, R6.2, R7.2, U$1.4
VX: JP2.2, U$1.1
X+: R3.1, R4.2, U$1.5
X-: R1.2, R2.1, U$1.6
Y+: R7.1, R8.2, U$1.7
Y-: R5.2, R6.1, U$1.8

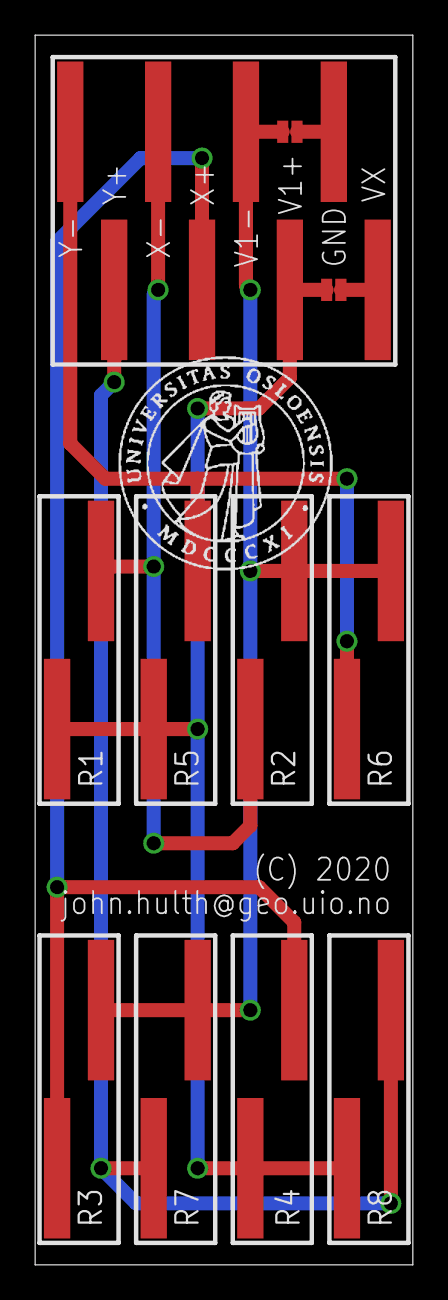
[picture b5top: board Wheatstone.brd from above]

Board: 2 copper layers, 21.5 x 70.0 mm, 12 parts (0 on the bottom side), 8 nets.

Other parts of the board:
U$3: UIO-LOGO-BL

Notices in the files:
SpotOn/Matrice 300 OSDK USBC/OSDK_USB-C.brd:
(C) 2021
SpotOn/Sensor PCB/Sensor PCB.brd:
(c) 2020
parts and their libraries:
microbuilder: This work is placed in the public domain, and may be freely used for commercial and non-commercial work with the following conditions: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
SparkFun-Connectors: Licensing: Creative Commons ShareAlike 4.0 International - https://creativecommons.org/licenses/by-sa/4.0
